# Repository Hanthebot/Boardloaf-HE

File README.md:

# Boardloaf-HE

Hall-effect variant of [Yuburoll's Boardloaf](https://github.com/yuburoll/Boardloaf), a 36-key split keyboard.

Wooting compatible, reversible, under 100mm pcb with qmk/vial support.

Based on Boardloaf and strongly inspired by [TrueStrike42](https://github.com/byungyoonc/TrueStrike42)

## Preparation
- Pricing: PCB based on JLCPCB / components based on Taobao (shipping to South Korea)
- Shipping fee not included, but PCB can be shipped with $1.5 option and Taobao delivery fee is acceptable for price gap
- Assumes you only want to build one (which makes cost higher)

### Board
| Component            | Qty | Price/unit          | Price |
| -------------------- | --- | ------------------- | ----- |
| PCB                  | 2   | $2/5 pcs            | $2    |
| SOT-23 SS49E         | 36  | ¥0.31/1 pc ~= $0.05 | $2    |
| SOIC-16 74HC4051(D)  | 6   | ¥0.74/1 pc ~= $0.11 | $0.7  |
| 0805 0.1uf capacitor | 42  | ¥2.5/50 pcs ~= $0.4 | $0.4  |
| PJ320A TRRS socket   | 2   | ¥8/100 pcs ~= $1.2  | $1.2  |
| RP2040 Zero          | 2   | ¥7.3/1 pc ~= $1.1   | $2.2  |
- For capacitor, 0.1~1uf should be fine
- And obviously, USB-C cable of your choice (with machine) and TRS/TRRS cable of your choice
- Board cost: $9 or more

### Case
- Option A: 3D printed case (from yuburoll's repo)
- Option B: Cheap plate cut
  - requires heat insert and standoff
  - 3T mdf panel of A4 size can fit 2x top & bottom plate
      - and costs about $1

| Component                  | Qty | Price/unit            | Price |
| -------------------------- | --- | --------------------- | ----- |
| M2 screw 6mm               | 16  | ¥4/500 pcs ~= $0.6    | $0.6  |
| M2 heat insert 3*3         | 16  | ¥4.9/100 pcs ~= $0.7  | $0.7  |
| M2 standoff 7mm + 3mm head | 16  | ¥2.31/50 pcs ~= $0.35 | $0.35 |
- Flathead screw was used
- Standoff can be shorter or longer - but I recommend 5mm at least
- Case cost: $3 or more

### Switches
| Component                          | Qty | Price/unit         | Price |
| ---------------------------------- | --- | ------------------ | ----- |
| Wooting compatible magnetic switch | 36  | ¥36/40 pcs ~= $5.3 | $5.3  |
- I personally chose Everglide Sticky Rice, as it was the cheapest I could find.
- While those without side pins should be fine, I'd use one with side pins so that they fix better
- Firmware fix may be required to use the opposite polarity
- Switch cost: $6 or more

With these things combined, you can get your own HE keyboard in about $12 excluding cables and switches.

## [Build guide](GUIDE.md)

## Features
- Supports both APC and rapid trigger
- Analog mouse keys driven by press depth: assign the stock Mouse/Wheel keycodes in Vial (hold Mouse Accel 0 for snipe); no webapp configuration required
- Cheap, simple, and working
- 3 multiplexor on each side, scanning 6 keys per mux

## Improvements to be done
- [x] Support analog mousekey
- [ ] Switch to full duplex / TRRS communication
- [x] Make SOT-23 pad larger, thus easier to solder
- [ ] ~~Switch to blackpill mcu for better ADC (not in this repo)~~

## Remarks
- Initial config recommendation: 30% / 20% / 20% / 10% / 10% / 20% (APC act / release; RT init dead / act offset / release offset / bottom dead)
- Documentation
  - Further documentation in progress
  - Plate KiCad file to be uploaded
  - Images to be added
- Case
  - PCB outline and holes are the same as original Boardloaf, thus all housing are compatible
  - I used cheap 3T mdf for housing, with bumpons. Works fine for me
- Random
  - PCB schematics are almost directly from TrueStrike42
  - If your board does not work, it's likely soldering issue. Try cleaning the board well and solder again
  - I think it's a good start on implementing random idea for HE keyboard

## Licenses
All code under firmware folder follows GPL v3.

Webapp is MIT license.

CC BY-SA 4.0 license for all hardware / design: inherited from Boardloaf

## Disclaimer
Webapp and firmware modification were vibe coded.
I checked it working.

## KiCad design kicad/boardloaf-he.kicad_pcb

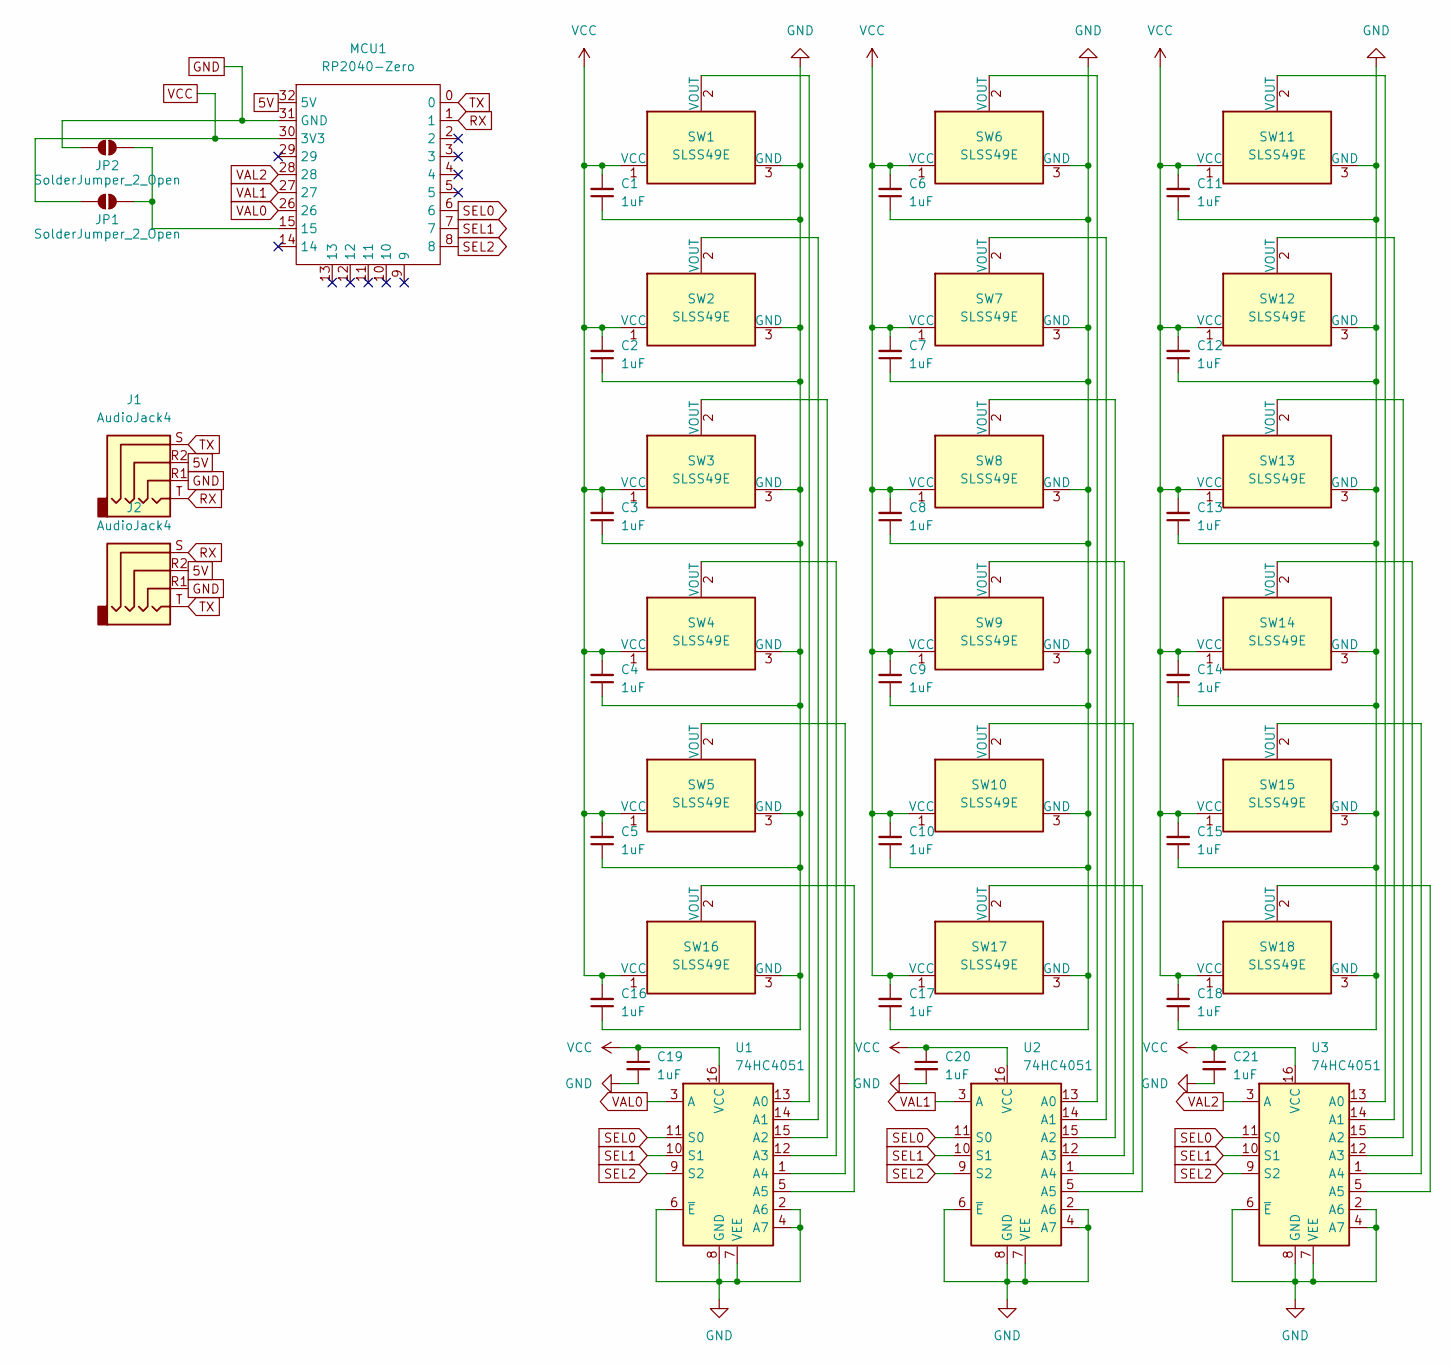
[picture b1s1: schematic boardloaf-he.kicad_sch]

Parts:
C1, C2, C3, C4, C5, C6, C7, C8, C9, C10, C11, C12, C13, C14, C15, C16, C17, C18, C19, C20, C21: 1uF; C_0805_2012Metric_Pad1.18x1.45mm_HandSolder
J1, J2: AudioJack4; TRRS-PJ-320A_PIN
JP1, JP2: SolderJumper_2_Open; SolderJumper-2_P1.3mm_Open_TrianglePad1.0x1.5mm
MCU1: RP2040-Zero; RP2040-Zero-RESIZED
SW1, SW2, SW3, SW4, SW5, SW6, SW7, SW8, SW9, SW10, SW11, SW12, SW13, SW14, SW15, SW16, SW17, SW18: SLSS49E; HE-Switch-1U
U1, U2, U3: 74HC4051; reversible-SOIC-16_3.9x9.9mm_P1.27mm

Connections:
5V: J1.R2, J2.R2, MCU1.32 (5V)
GND: C1.1, C2.1, C3.1, C4.1, C5.1, C6.1, C7.1, C8.1, C9.1, C10.1, C11.1, C12.1, C13.1, C14.1, C15.1, C16.1, C17.1, C18.1, C19.2, C20.2, C21.2, J1.R1, J2.R1, JP2.1 (A), MCU1.31 (GND), SW1.3 (GND), SW2.3 (GND), SW3.3 (GND), SW4.3 (GND), SW5.3 (GND), SW6.3 (GND), SW7.3 (GND), SW8.3 (GND), SW9.3 (GND), SW10.3 (GND), SW11.3 (GND), SW12.3 (GND), SW13.3 (GND), SW14.3 (GND), SW15.3 (GND), SW16.3 (GND), SW17.3 (GND), SW18.3 (GND), U1.2 (A6), U1.4 (A7), U1.6 (~E), U1.7 (VEE), U1.8 (GND), U2.2 (A6), U2.4 (A7), U2.6 (~E), U2.7 (VEE), U2.8 (GND), U3.2 (A6), U3.4 (A7), U3.6 (~E), U3.7 (VEE), U3.8 (GND)
unnamed: JP1.2 (B), JP2.2 (B), MCU1.15
unnamed: SW1.2 (VOUT), U1.13 (A0)
unnamed: SW2.2 (VOUT), U1.14 (A1)
unnamed: SW3.2 (VOUT), U1.15 (A2)
unnamed: SW4.2 (VOUT), U1.12 (A3)
unnamed: SW5.2 (VOUT), U1.1 (A4)
unnamed: SW6.2 (VOUT), U2.13 (A0)
unnamed: SW7.2 (VOUT), U2.14 (A1)
unnamed: SW8.2 (VOUT), U2.15 (A2)
unnamed: SW9.2 (VOUT), U2.12 (A3)
unnamed: SW10.2 (VOUT), U2.1 (A4)
unnamed: SW11.2 (VOUT), U3.13 (A0)
unnamed: SW12.2 (VOUT), U3.14 (A1)
unnamed: SW13.2 (VOUT), U3.15 (A2)
unnamed: SW14.2 (VOUT), U3.12 (A3)
unnamed: SW15.2 (VOUT), U3.1 (A4)
unnamed: SW16.2 (VOUT), U1.5 (A5)
unnamed: SW17.2 (VOUT), U2.5 (A5)
unnamed: SW18.2 (VOUT), U3.5 (A5)
RX: J1.T, J2.S, MCU1.1
SEL0: MCU1.6, U1.11 (S0), U2.11 (S0), U3.11 (S0)
SEL1: MCU1.7, U1.10 (S1), U2.10 (S1), U3.10 (S1)
SEL2: MCU1.8, U1.9 (S2), U2.9 (S2), U3.9 (S2)
TX: J1.S, J2.T, MCU1.0
VAL0: MCU1.26, U1.3 (A)
VAL1: MCU1.27, U2.3 (A)
VAL2: MCU1.28, U3.3 (A)
VCC: C1.2, C2.2, C3.2, C4.2, C5.2, C6.2, C7.2, C8.2, C9.2, C10.2, C11.2, C12.2, C13.2, C14.2, C15.2, C16.2, C17.2, C18.2, C19.1, C20.1, C21.1, JP1.1 (A), MCU1.30 (3V3), SW1.1 (VCC), SW2.1 (VCC), SW3.1 (VCC), SW4.1 (VCC), SW5.1 (VCC), SW6.1 (VCC), SW7.1 (VCC), SW8.1 (VCC), SW9.1 (VCC), SW10.1 (VCC), SW11.1 (VCC), SW12.1 (VCC), SW13.1 (VCC), SW14.1 (VCC), SW15.1 (VCC), SW16.1 (VCC), SW17.1 (VCC), SW18.1 (VCC), U1.16 (VCC), U2.16 (VCC), U3.16 (VCC)

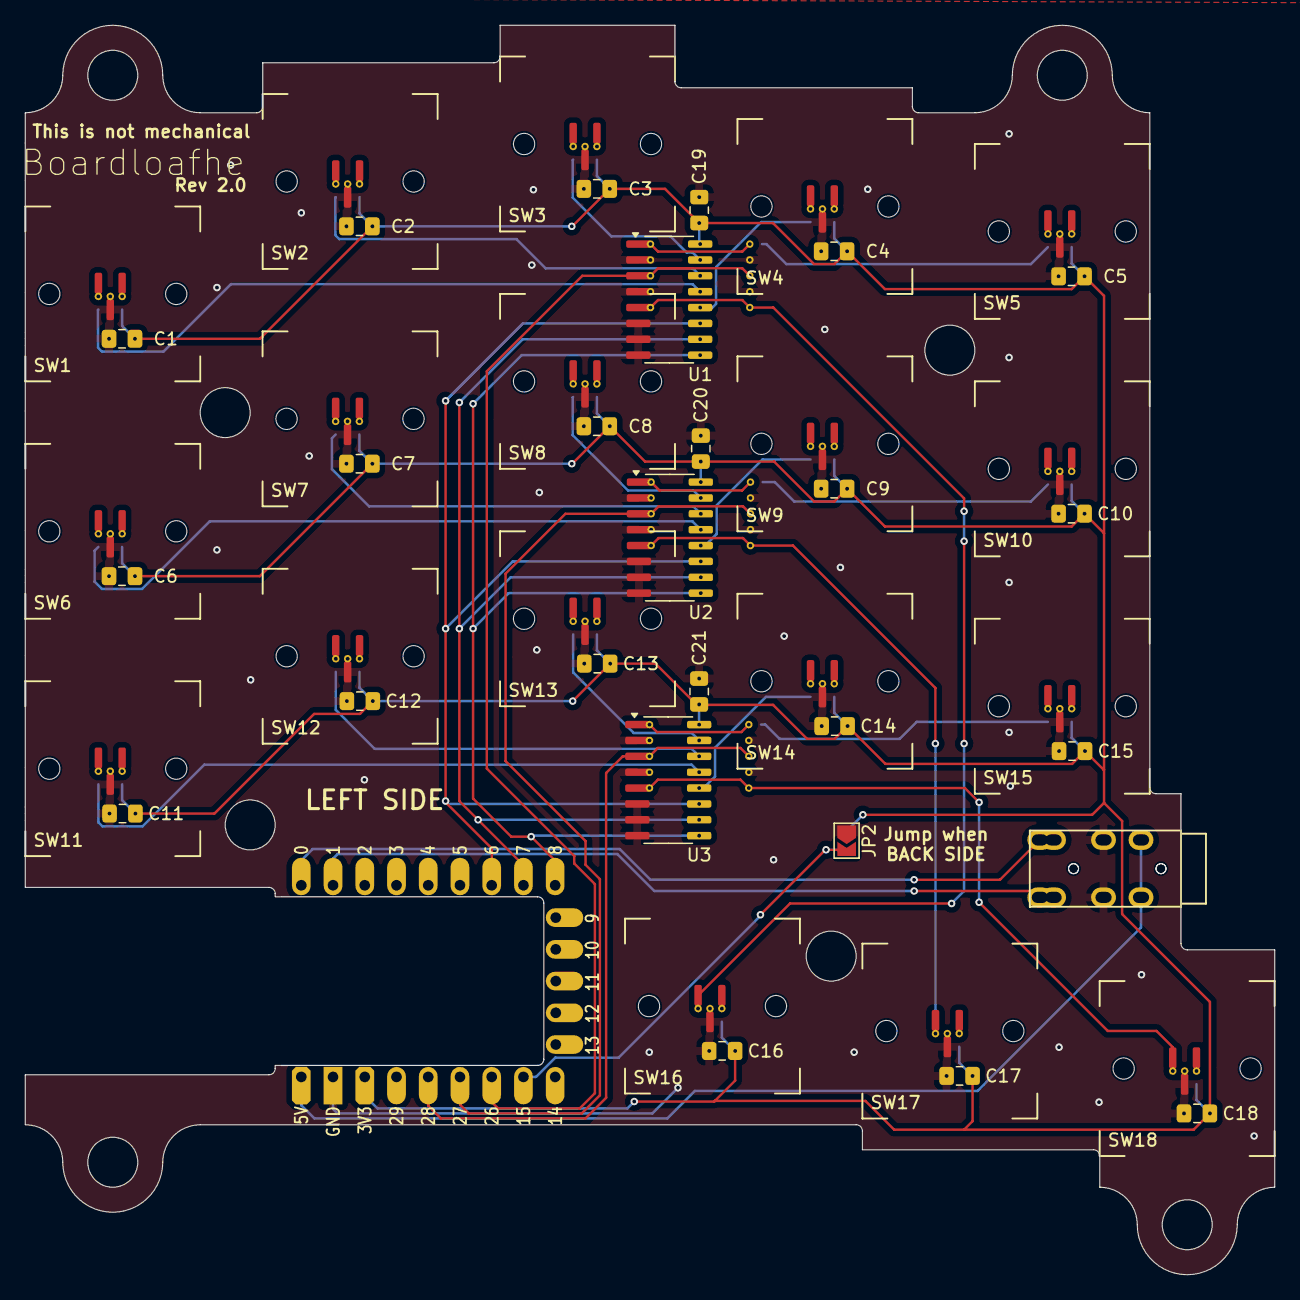
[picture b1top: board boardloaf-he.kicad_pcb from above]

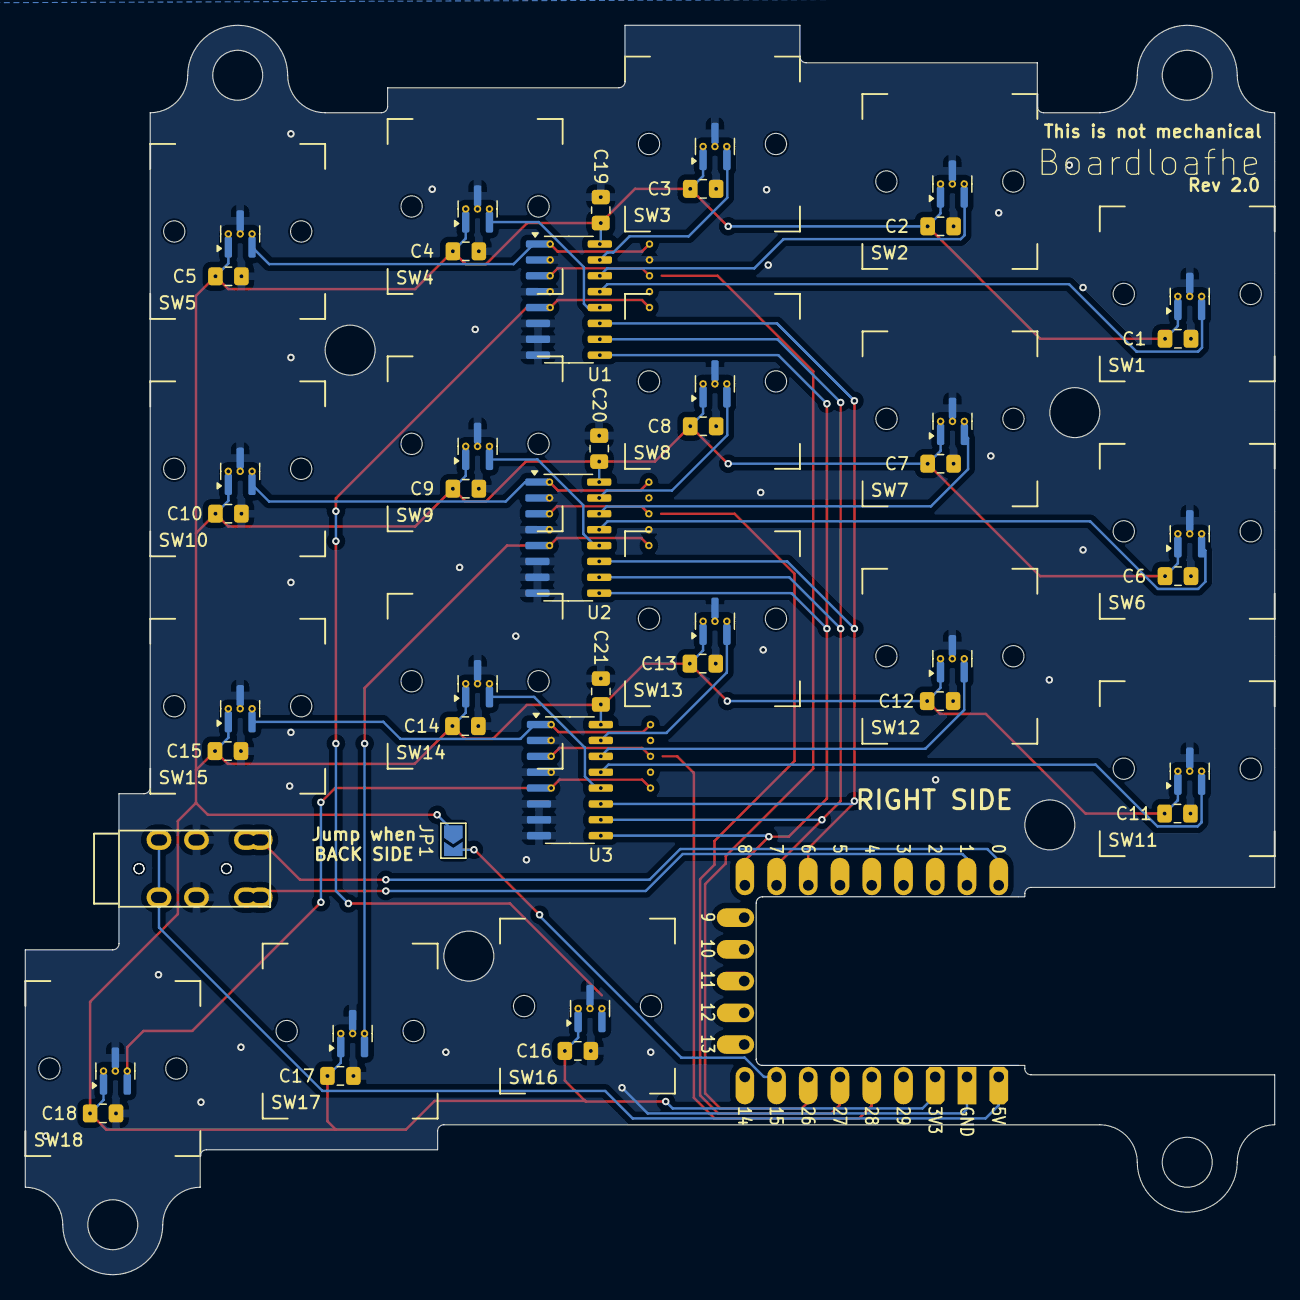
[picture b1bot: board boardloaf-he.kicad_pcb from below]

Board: 2 copper layers, 100.0 x 100.0 mm, 47 parts (2 on the bottom side), 30 nets.
